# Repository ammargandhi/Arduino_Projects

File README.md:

# Arduino_Projects
Small Arduino Based Projects

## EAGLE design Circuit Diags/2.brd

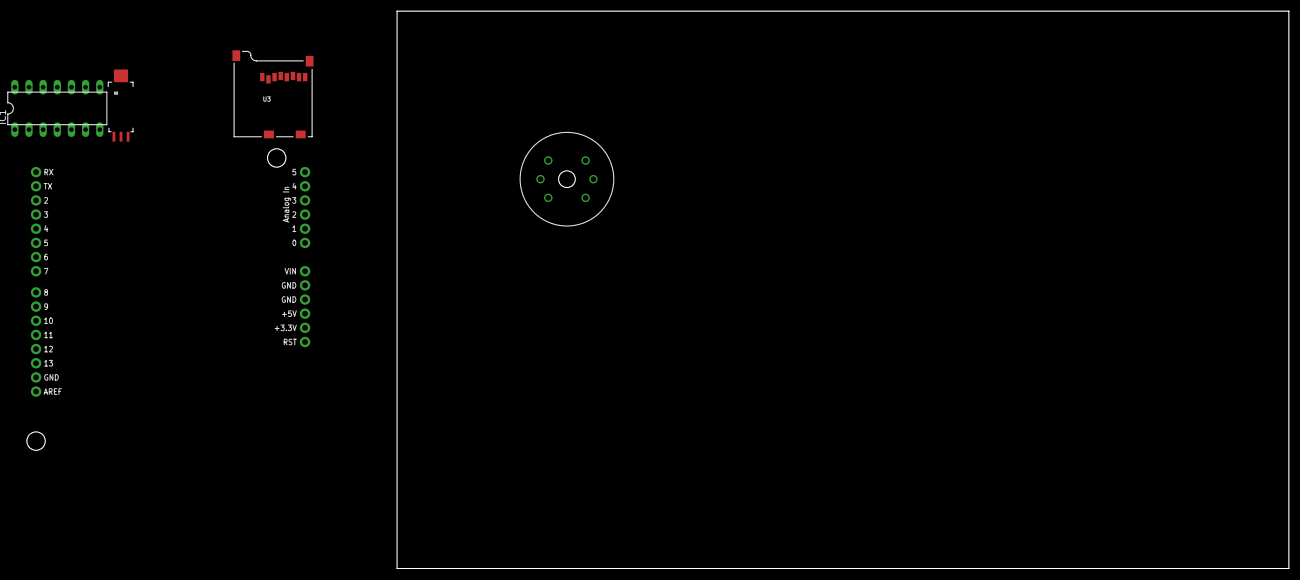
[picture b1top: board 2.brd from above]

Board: 2 copper layers, 160.0 x 100.0 mm, 5 parts (0 on the bottom side), 4 nets, no tracks yet.

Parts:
IC1: 74AC125N; DIL14
U1: GAS_SENSOR; MQ-3
U2: HIH-4030SMD; HIH-4030
U3: USD-SOCKETNEW; MICRO-SD-SOCKET-PP
U4: ARDUINO_SHIELDLABEL; DUEMILANOVE_SHIELD

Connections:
A0: U1.B1, U4.A0
A1: U2.2, U4.A1
GND: IC1.7, U1.HB, U2.1
VDD: IC1.1, IC1.4, IC1.10, IC1.13, U1.A1, U1.HA, U2.3

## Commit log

2016-03-31 Added files via upload

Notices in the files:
parts and their libraries:
SparkFun: Licensing: CC v3.0 Share-Alike You are welcome to use this library for commercial purposes.
